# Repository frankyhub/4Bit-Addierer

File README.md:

# 4Bit-Addierer
Projekt Gymnasium Tegernsee

## [Link zur Dokumentation PDF](https://github.com/frankyhub/4Bit-Addierer/blob/main/doc/4-Bit-Addierer-Dokumentation.pdf)

## Frontplatte

## PCB

## Schaltplan Volladdierer

## Schaltplan vier Volladdierer

## 4Bit-Addierer im Gehäuse

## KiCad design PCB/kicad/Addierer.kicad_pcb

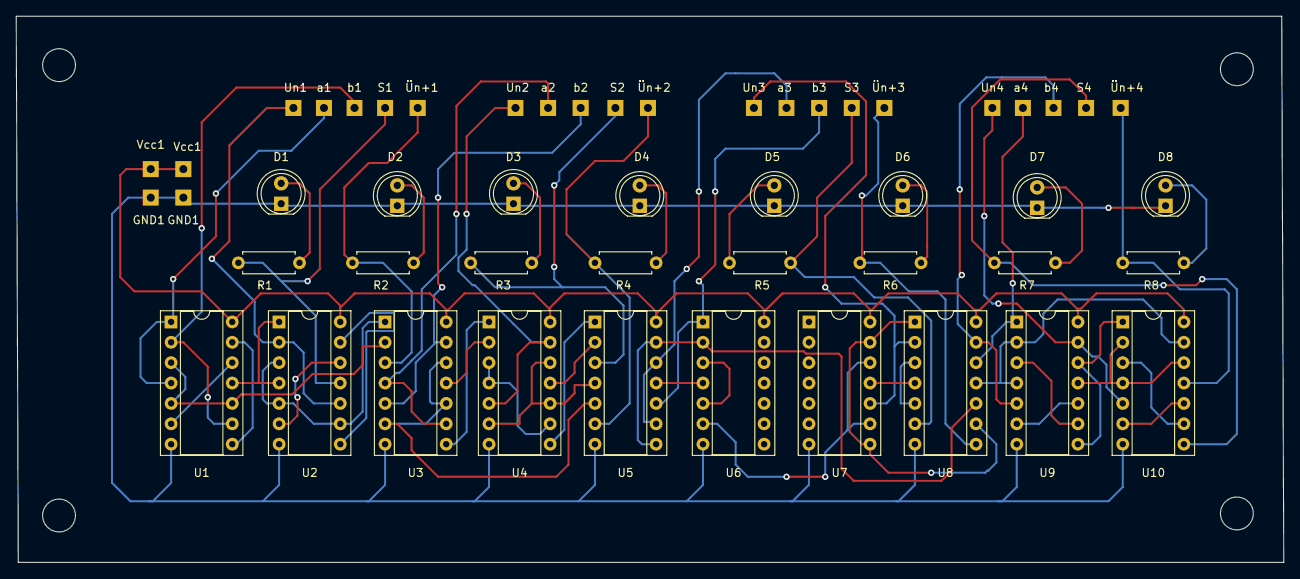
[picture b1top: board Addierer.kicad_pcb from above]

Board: 2 copper layers, 158.0 x 68.1 mm, 50 parts (0 on the bottom side), 58 nets.

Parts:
D1, D2, D3, D4, D5, D6, D7, D8: LED; LED_D5.0mm
GND1, GND1#2: LP_GND; LP
R1, R2, R3, R4, R5, R6, R7, R8: R; R_Axial_DIN0207_L6.3mm_D2.5mm_P7.62mm_Horizontal
S1: S1; LP
S2: S2; LP
S3: S3; LP
S4: S4; LP
U1, U2, U3, U4, U5, U6, U7, U8, U9, U10: 74LS00; DIP-14_W7.62mm_Socket
Un1, Un2, Un3, Un4: LP_A; LP
Vcc1, Vcc1#2: LP_VCC; LP
a1, a2, a3, a4: LP_A; LP
b1, b2, b3, b4: LP_A; LP
Ün+1: Ün+1; LP
Ün+2: Ün+2; LP
Ün+3: Ün+3; LP
Ün+4: Ün+4; LP

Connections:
+5V: U1.14, U2.14, U3.14, U4.14, U5.14, U6.14, U7.14, U8.14, U9.14, U10.14, Vcc1.1, Vcc1#2.1
GND: D1.1, D2.1, D3.1, D4.1, D5.1, D6.1, D7.1, D8.1, GND1.1, GND1#2.1, U1.7, U2.7, U3.7, U4.7, U5.7, U6.7, U7.7, U8.7, U9.7, U10.7
unnamed: D1.2, R1.2
unnamed: D2.2, R2.2
unnamed: D3.2, R3.2
unnamed: D4.2, R4.2
unnamed: D5.2, R5.2
unnamed: D6.2, R6.2
unnamed: D7.2, R7.2
unnamed: D8.2, R8.2
unnamed: R1.1, S1.1, U2.11
unnamed: R2.1, U3.3, Ün+1.1
unnamed: R3.1, S2.1, U5.3
unnamed: R4.1, U5.6, Ün+2.1
unnamed: R5.1, S3.1, U8.6
unnamed: R6.1, U8.8, Ün+3.1
unnamed: R7.1, S4.1, U10.8
unnamed: R8.1, U10.11, Ün+4.1
unnamed: U1.1, U1.4, a1.1
unnamed: U1.2, U1.9, b1.1
unnamed: U1.3, U1.5, U1.10, U3.2
unnamed: U1.11, U2.1, U2.4
unnamed: U1.6, U1.12
unnamed: U1.8, U1.13
unnamed: U2.3, U2.5, U2.9, U3.1
unnamed: U2.2, U2.10, Un1.1
unnamed: U2.6, U2.12
unnamed: U2.8, U2.13
unnamed: U3.4, U3.9, a2.1
unnamed: U3.8, U4.1
unnamed: U3.6, U3.10, U3.12, U5.5
unnamed: U3.11, U4.2
unnamed: U3.5, U3.13, b2.1
unnamed: U4.3, U4.4, U4.9
unnamed: U4.8, U5.1
unnamed: U4.6, U4.10, U4.12, U5.4
unnamed: U4.11, U5.2
unnamed: U4.5, U4.13, Un2.1
unnamed: U5.10, U6.1, b3.1
unnamed: U5.11, U6.4
unnamed: U5.9, U5.12, a3.1
unnamed: U5.8, U5.13, U6.2, U8.10
unnamed: U6.3, U6.5
unnamed: U6.6, U7.9, U7.12
unnamed: U7.10, U8.2, Un3.1
unnamed: U7.11, U8.4
unnamed: U7.8, U7.13, U8.1, U8.9
unnamed: U8.3, U8.5
unnamed: U8.12, U9.1, a4.1
unnamed: U8.13, U9.5, b4.1
unnamed: U9.3, U9.9
unnamed: U9.6, U9.10
unnamed: U9.8, U9.12, U10.1
unnamed: U10.3, U10.9
unnamed: U9.13, U10.5, Un4.1
unnamed: U10.6, U10.10
unnamed: U9.11, U10.2, U10.4, U10.12
unnamed: U8.11, U9.2, U9.4, U10.13
